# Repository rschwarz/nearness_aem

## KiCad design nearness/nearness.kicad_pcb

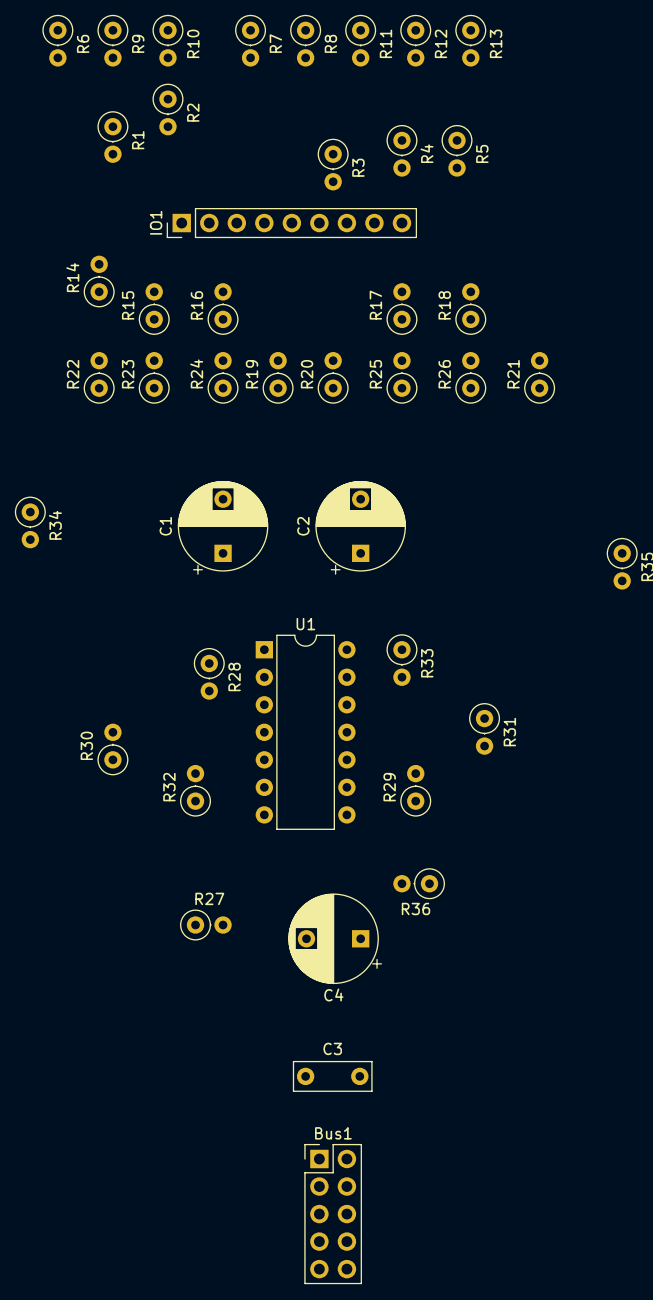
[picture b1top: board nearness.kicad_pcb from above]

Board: 2 copper layers, 43 parts (0 on the bottom side), 32 nets, no tracks yet.

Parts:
Bus1: Conn_02x05_Counter_Clockwise; PinHeader_2x05_P2.54mm_Vertical
C1, C2: 1u; CP_Radial_D8.0mm_P5.00mm
C3: 100n; C_Disc_D7.0mm_W2.5mm_P5.00mm
C4: 10u; CP_Radial_D8.0mm_P5.00mm
IO1: Conn_01x09; PinHeader_1x09_P2.54mm_Vertical
R1, R18: 47K; R_Axial_DIN0207_L6.3mm_D2.5mm_P2.54mm_Vertical
R2, R9, R10, R17, R25, R26: 56K; R_Axial_DIN0207_L6.3mm_D2.5mm_P2.54mm_Vertical
R3, R16: 33K; R_Axial_DIN0207_L6.3mm_D2.5mm_P2.54mm_Vertical
R4, R12, R15, R23: 220K; R_Axial_DIN0207_L6.3mm_D2.5mm_P2.54mm_Vertical
R5, R8, R14, R19: 680K; R_Axial_DIN0207_L6.3mm_D2.5mm_P2.54mm_Vertical
R6, R21, R28, R29, R30, R31, R32, R33: 100K; R_Axial_DIN0207_L6.3mm_D2.5mm_P2.54mm_Vertical
R7, R11, R20, R24: 180K; R_Axial_DIN0207_L6.3mm_D2.5mm_P2.54mm_Vertical
R13, R22: 1M; R_Axial_DIN0207_L6.3mm_D2.5mm_P2.54mm_Vertical
R27, R36: 4K7; R_Axial_DIN0207_L6.3mm_D2.5mm_P2.54mm_Vertical
R34, R35: 1K; R_Axial_DIN0207_L6.3mm_D2.5mm_P2.54mm_Vertical
U1: LM324; DIP-14_W7.62mm

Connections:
+5V: Bus1.1, C3.1, R27.1, U1.4
/Left: C1.2, R6.1, R7.1, R8.1, R9.1, R10.1, R11.1, R12.1, R13.1
/Right: C2.2, R19.1, R20.1, R21.1, R22.1, R23.1, R24.1, R25.1, R26.1
/VGnd: C4.2, R27.2, R36.1, U1.2, U1.6, U1.9, U1.13
GND: Bus1.2, C3.2, C4.1, R36.2, U1.11
unnamed: C1.1, R28.2, U1.3
unnamed: C2.1, R29.2, U1.10
unnamed: IO1.2, R6.2, R14.2
unnamed: IO1.3, R1.2, R15.2
unnamed: IO1.4, R2.2, R16.2
unnamed: IO1.5, R7.2, R8.2, R19.2, R20.2
unnamed: IO1.6, R3.2, R17.2
unnamed: IO1.7, R4.2, R18.2
unnamed: IO1.8, R5.2, R21.2
unnamed: R1.1, R9.2
unnamed: R2.1, R10.2
unnamed: R3.1, R11.2
unnamed: R4.1, R12.2
unnamed: R5.1, R13.2
unnamed: R14.1, R22.2
unnamed: R15.1, R23.2
unnamed: R16.1, R24.2
unnamed: R17.1, R25.2
unnamed: R18.1, R26.2
unnamed: R28.1, R30.2, U1.1
unnamed: R29.1, R31.2, U1.8
unnamed: R30.1, R32.2, U1.5
unnamed: R31.1, R33.2, U1.12
unnamed: R32.1, R34.2, U1.7
unnamed: R33.1, R35.2, U1.14
OutL: IO1.1, R34.1
OutR: IO1.9, R35.1

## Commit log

2024-06-19 add manuals for Eurorack modules
2024-06-19 add schematics for AEM mixer and Nearness
2024-06-19 add requirements.txt
2024-06-19 add another nearness schematic
    has same resistor values, but is easier to read?!
2024-06-19 add notebook about resistor <> panning mapping
2024-06-20 add notebook for resistor combinations
2024-07-16 Write down resistor combinations
2024-07-16 add first schematic
2024-07-16 schematics: add footprints
2024-07-16 schematics: user proper pin headers with vertical footprint
2024-07-16 schematics: use LM324 instead of 4*LM321
2024-07-16 schematics: connect only one each to bus
2024-07-16 pcb: first attempt at layout
2024-07-18 schematic: fix orientation of op-amps
